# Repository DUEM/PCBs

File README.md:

# PCBs
A working record of DUSC PCBs and the DUEM KiCad library. Hopefully this way we can keep KiCad happy by all singing from the same ~~hymnsheet~~ netlist. Old and not necessarily a complete set of PCBs live in `oldPCBs`.

Remember to store final designs on the DUSC drive.

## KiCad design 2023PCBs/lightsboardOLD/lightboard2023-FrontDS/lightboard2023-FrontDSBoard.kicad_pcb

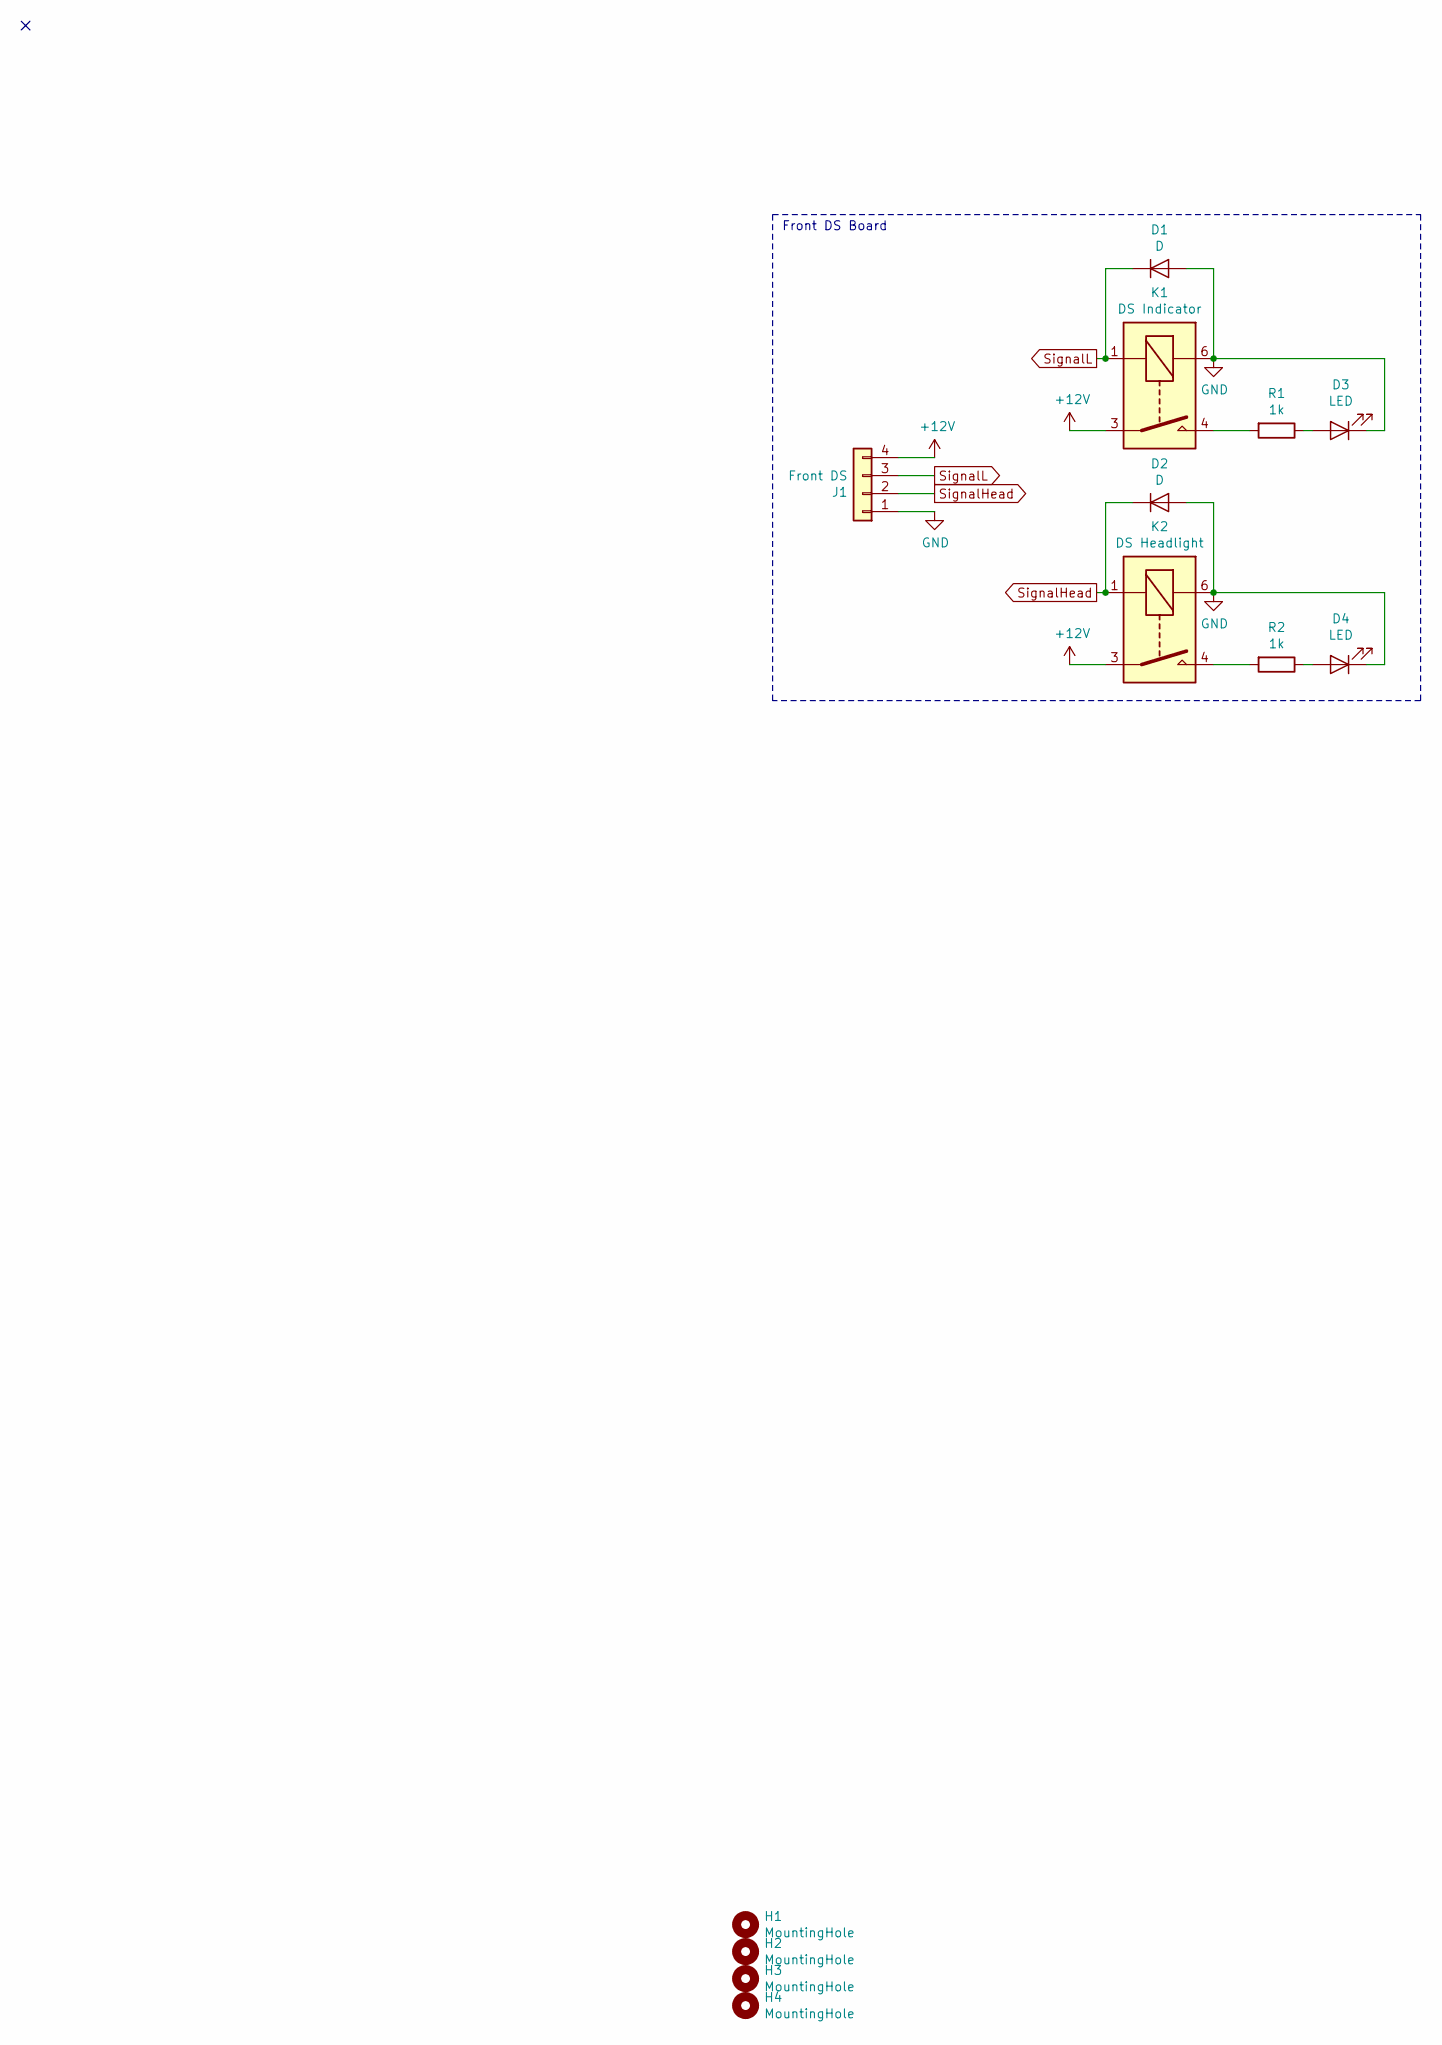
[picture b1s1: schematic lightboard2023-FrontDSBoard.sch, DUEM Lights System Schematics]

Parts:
D1, D2: D; D_DO-41_SOD81_P10.16mm_Horizontal
D3, D4: LED; flywire_2
H1, H2, H3, H4: MountingHole; MountingHole_2.7mm
J1: Front DS; Phoenix_4Way_P2.5mm
K1: DS Indicator; DK_Relay
K2: DS Headlight; DK_Relay
R1, R2: 1k; R_Axial_DIN0207_L6.3mm_D2.5mm_P10.16mm_Horizontal

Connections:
+12V: J1.4, K1.3, K2.3
GND: D1.2 (A), D2.2 (A), D3.1 (K), D4.1 (K), J1.1, K1.6, K2.6
unnamed: D3.2 (A), R1.1
unnamed: D4.2 (A), R2.1
unnamed: K1.4, R1.2
unnamed: K2.4, R2.2
SignalHead: D2.1 (K), J1.2, K2.1
SignalL: D1.1 (K), J1.3, K1.1

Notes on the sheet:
Front DS Board

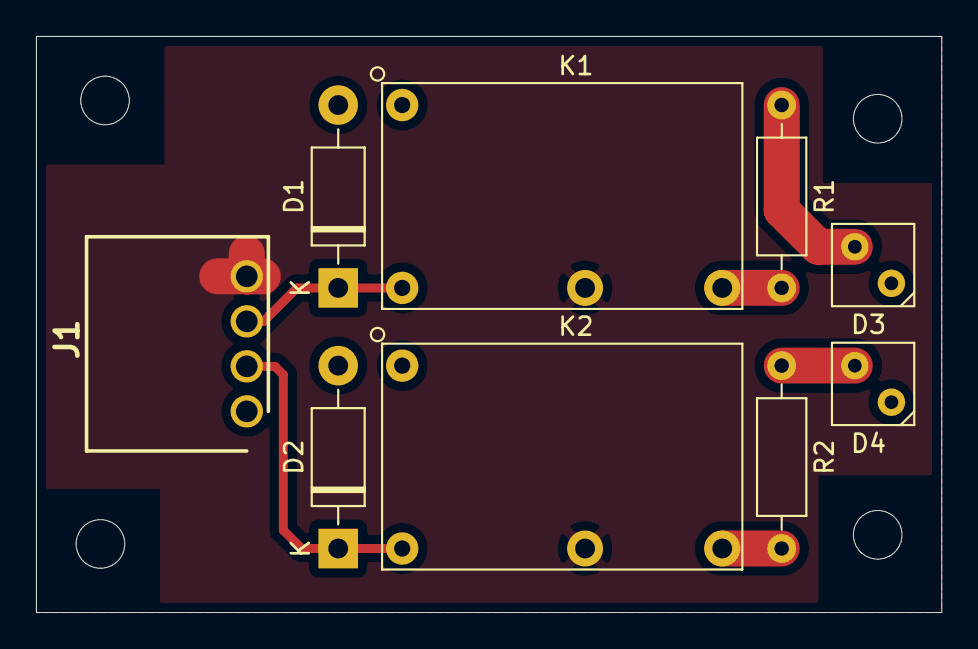
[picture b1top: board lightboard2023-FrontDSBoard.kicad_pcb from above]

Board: 2 copper layers, 50.3 x 32.0 mm, 13 parts (0 on the bottom side), 8 nets.

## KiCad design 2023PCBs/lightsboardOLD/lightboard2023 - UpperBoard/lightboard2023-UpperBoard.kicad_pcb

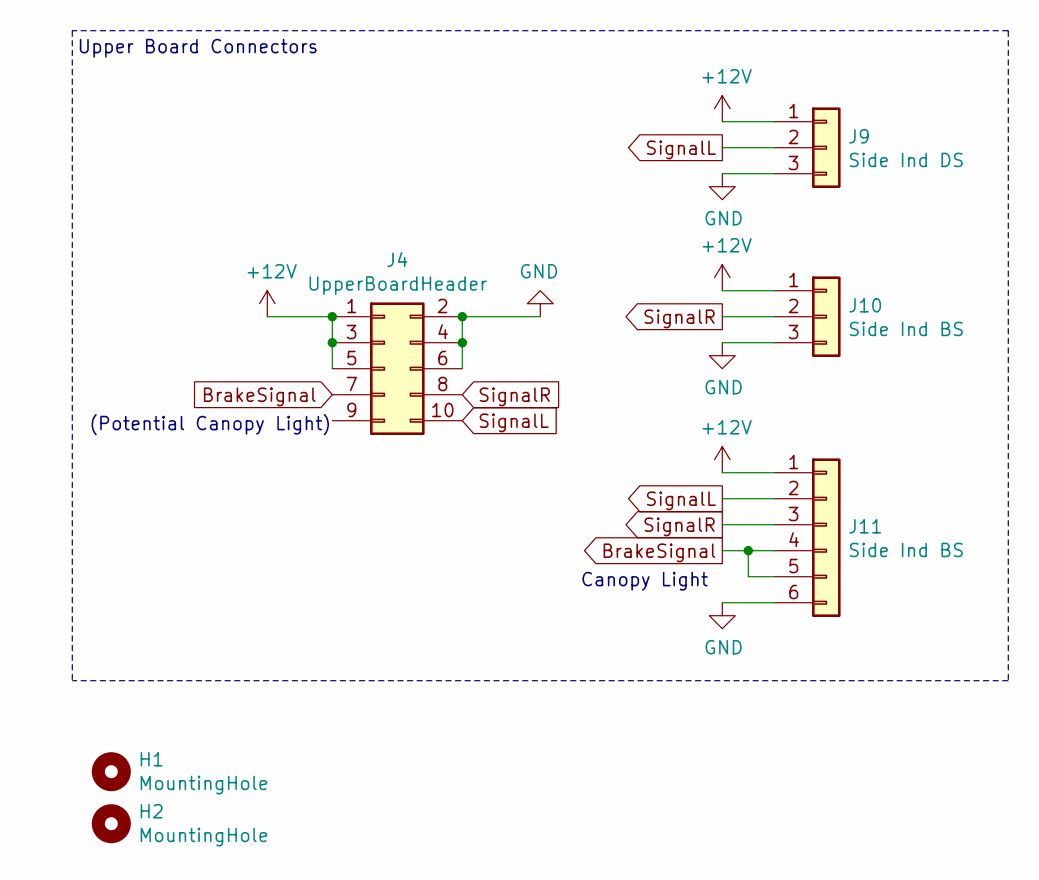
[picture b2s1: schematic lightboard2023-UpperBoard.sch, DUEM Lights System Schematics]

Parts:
H1, H2: MountingHole; MountingHole_2.7mm
J4: UpperBoardHeader; PinHeader_2x05_P2.54mm_Vertical
J9: Side Ind DS; Phoenix_3Way_P2.5mm
J10: Side Ind BS; Phoenix_3Way_P2.5mm
J11: Side Ind BS; Phoenix_6Way_P2.5mm

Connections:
+12V: J4.1, J4.3, J4.5, J9.1, J10.1, J11.1
BrakeSignal: J4.7, J11.4, J11.5
GND: J4.2, J4.4, J4.6, J9.3, J10.3, J11.6
SignalL: J4.10, J9.2, J11.2
SignalR: J4.8, J10.2, J11.3

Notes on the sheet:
Upper Board Connectors
(Potential Canopy Light)
Canopy Light

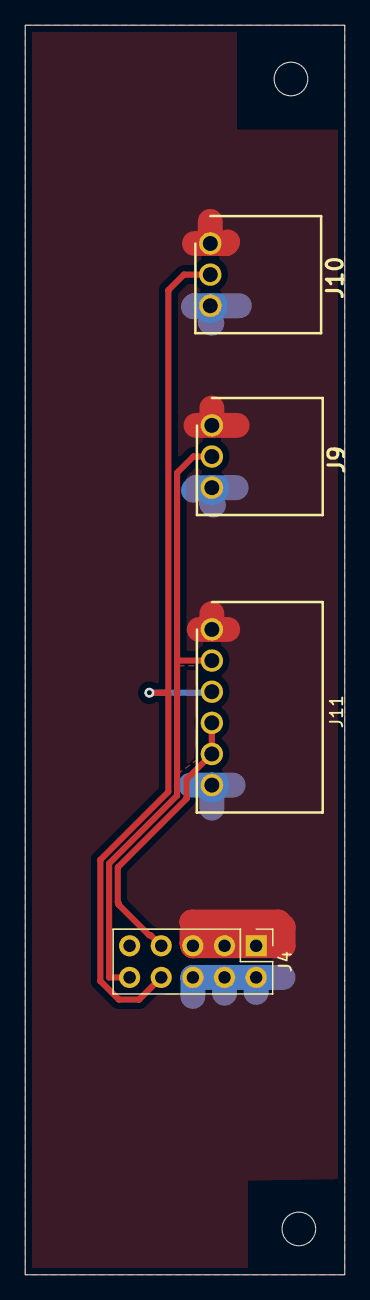
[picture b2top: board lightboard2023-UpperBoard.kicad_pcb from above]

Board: 2 copper layers, 25.7 x 100.3 mm, 6 parts (0 on the bottom side), 5 nets.

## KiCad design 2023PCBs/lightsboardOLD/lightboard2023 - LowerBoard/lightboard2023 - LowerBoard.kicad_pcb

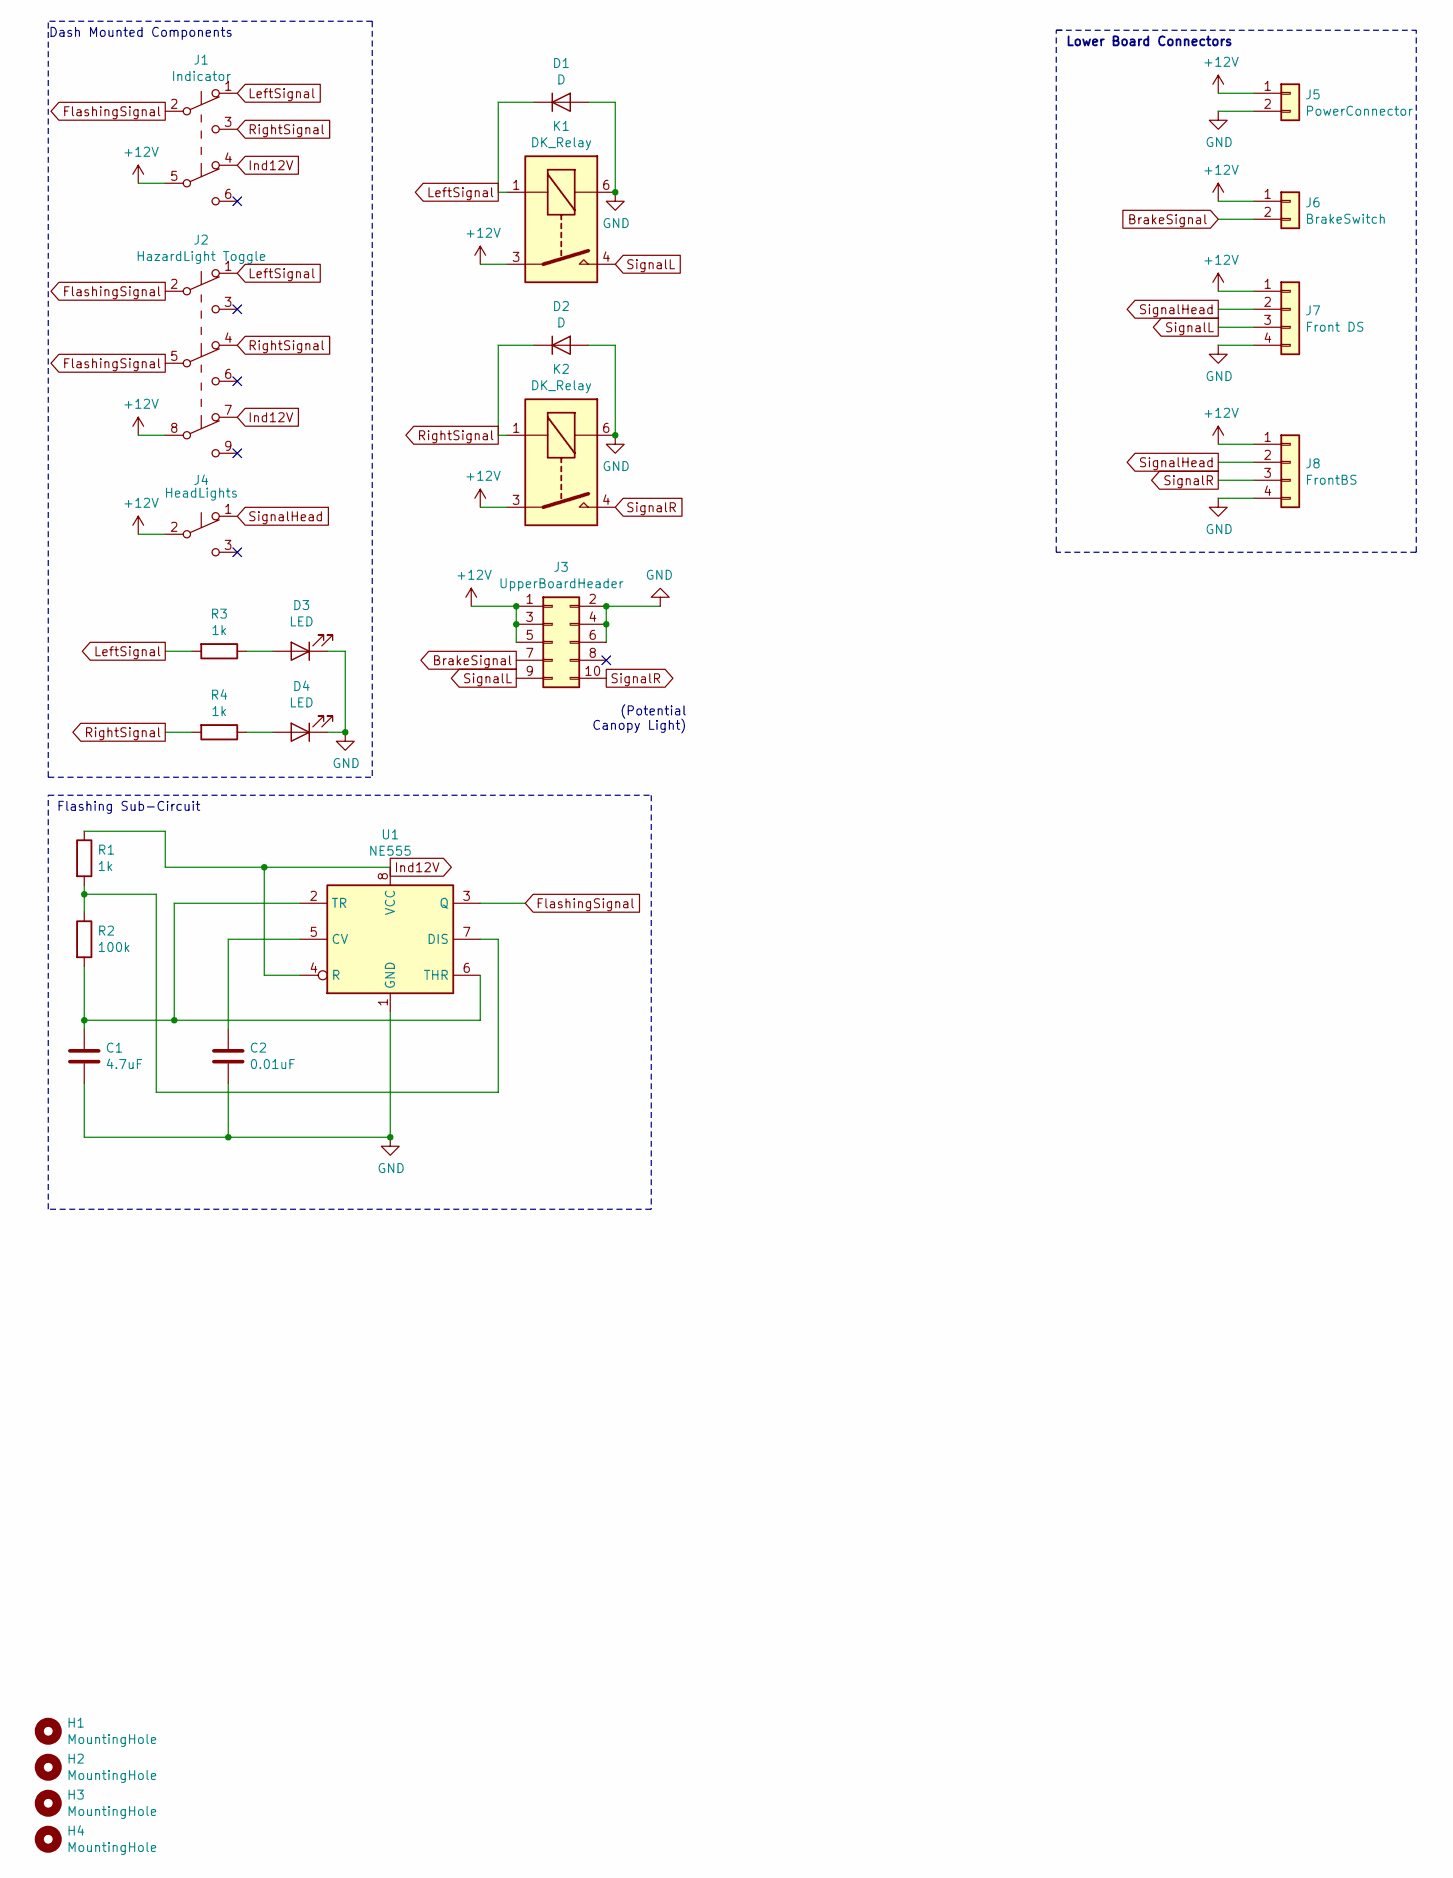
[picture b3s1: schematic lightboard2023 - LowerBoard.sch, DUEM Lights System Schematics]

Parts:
C1: 4.7uF; CP_Radial_D5.0mm_P2.50mm
C2: 0.01uF; CP_Radial_D5.0mm_P2.50mm
D1, D2: D; D_DO-41_SOD81_P10.16mm_Horizontal
D3, D4: LED; flywire_2
H1, H2, H3, H4: MountingHole; MountingHole_2.7mm
J1: Indicator; flywire_5
J2: HazardLight Toggle; flywire_6_special_haz
J3: UpperBoardHeader; PinHeader_2x05_P2.54mm_Vertical
J4: HeadLights; flywire_3
J5: PowerConnector; Phoenix_2Way_P2.5mm
J6: BrakeSwitch; Phoenix_2Way_P2.5mm
J7: Front DS; Phoenix_4Way_P2.5mm
J8: FrontBS; Phoenix_4Way_P2.5mm
K1, K2: DK_Relay
R1, R3, R4: 1k; R_Axial_DIN0207_L6.3mm_D2.5mm_P10.16mm_Horizontal
R2: 100k; R_Axial_DIN0207_L6.3mm_D2.5mm_P10.16mm_Horizontal
U1: NE555; DIP-8_W7.62mm_Socket

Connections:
+12V: J1.5 (B), J2.8 (B), J3.1, J3.3, J3.5, J4.2 (B), J5.1, J6.1, J7.1, J8.1, K1.3, K2.3
BrakeSignal: J3.7, J6.2
FlashingSignal: J1.2 (B), J2.2 (B), J2.5 (B), U1.3 (Q)
GND: C1.2, C2.2, D1.2 (A), D2.2 (A), D3.1 (K), D4.1 (K), J3.2, J3.4, J3.6, J5.2, J7.4, J8.4, K1.6, K2.6, U1.1 (GND)
Ind12V: J1.4 (A), J2.7 (A), R1.1, U1.4 (R), U1.8 (VCC)
LeftSignal: D1.1 (K), J1.1 (A), J2.1 (A), K1.1, R3.2
unnamed: C1.1, R2.2, U1.2 (TR), U1.6 (THR)
unnamed: C2.1, U1.5 (CV)
unnamed: D3.2 (A), R3.1
unnamed: D4.2 (A), R4.1
unnamed: R1.2, R2.1, U1.7 (DIS)
RightSignal: D2.1 (K), J1.3 (C), J2.4 (A), K2.1, R4.2
SignalHead: J4.1 (A), J7.2, J8.2
SignalL: J3.9, J7.3, K1.4
SignalR: J3.10, J8.3, K2.4

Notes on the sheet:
Lower Board Connectors
(Potential Canopy Light)
Flashing Sub-Circuit
Dash Mounted Components

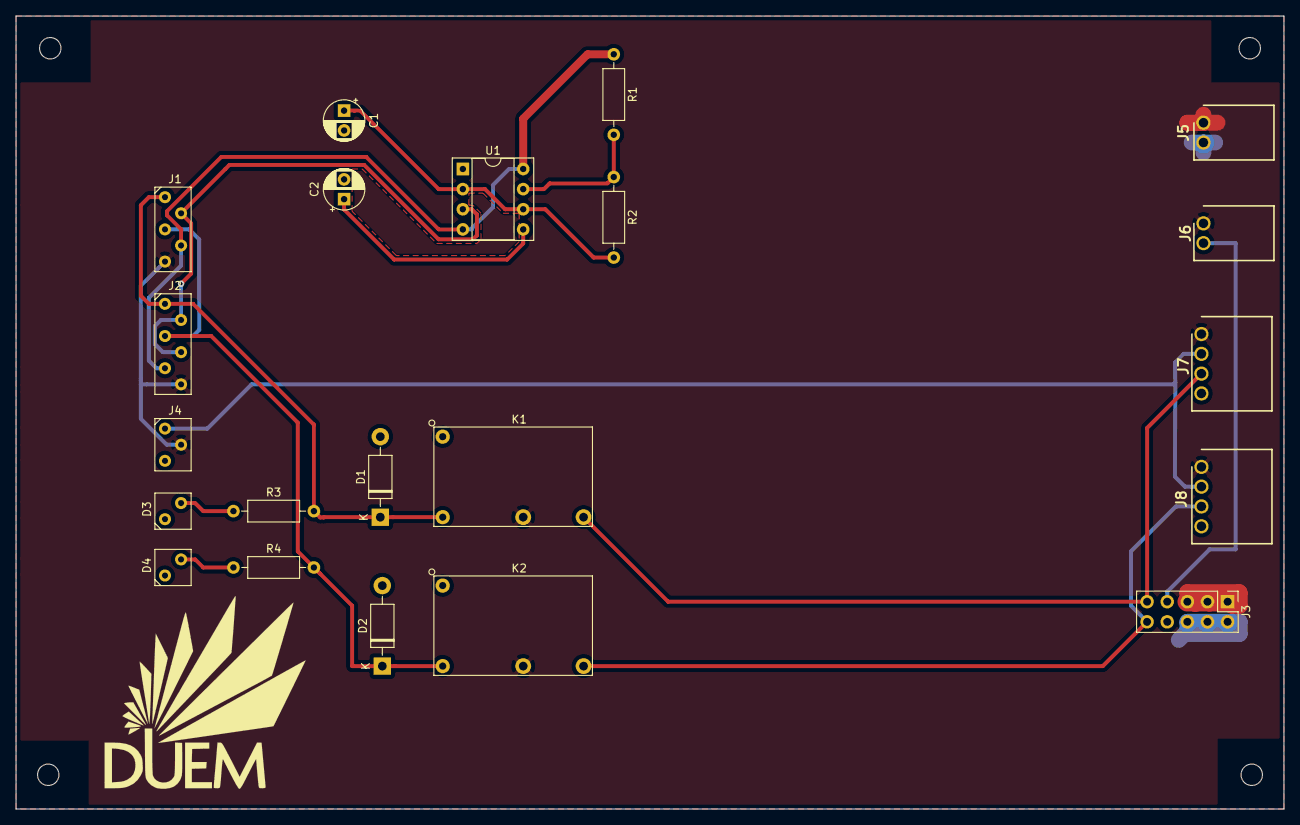
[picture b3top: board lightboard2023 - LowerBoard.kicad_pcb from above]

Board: 2 copper layers, 160.0 x 100.1 mm, 25 parts (0 on the bottom side), 15 nets.

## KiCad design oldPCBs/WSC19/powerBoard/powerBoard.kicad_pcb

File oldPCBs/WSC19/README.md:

# WSC19
Am going to try and put the original WSC19 design files in here. KiCad will probably cry when you open these... hopefully demonstrating why we're trying to use a global KiCad library instead now.

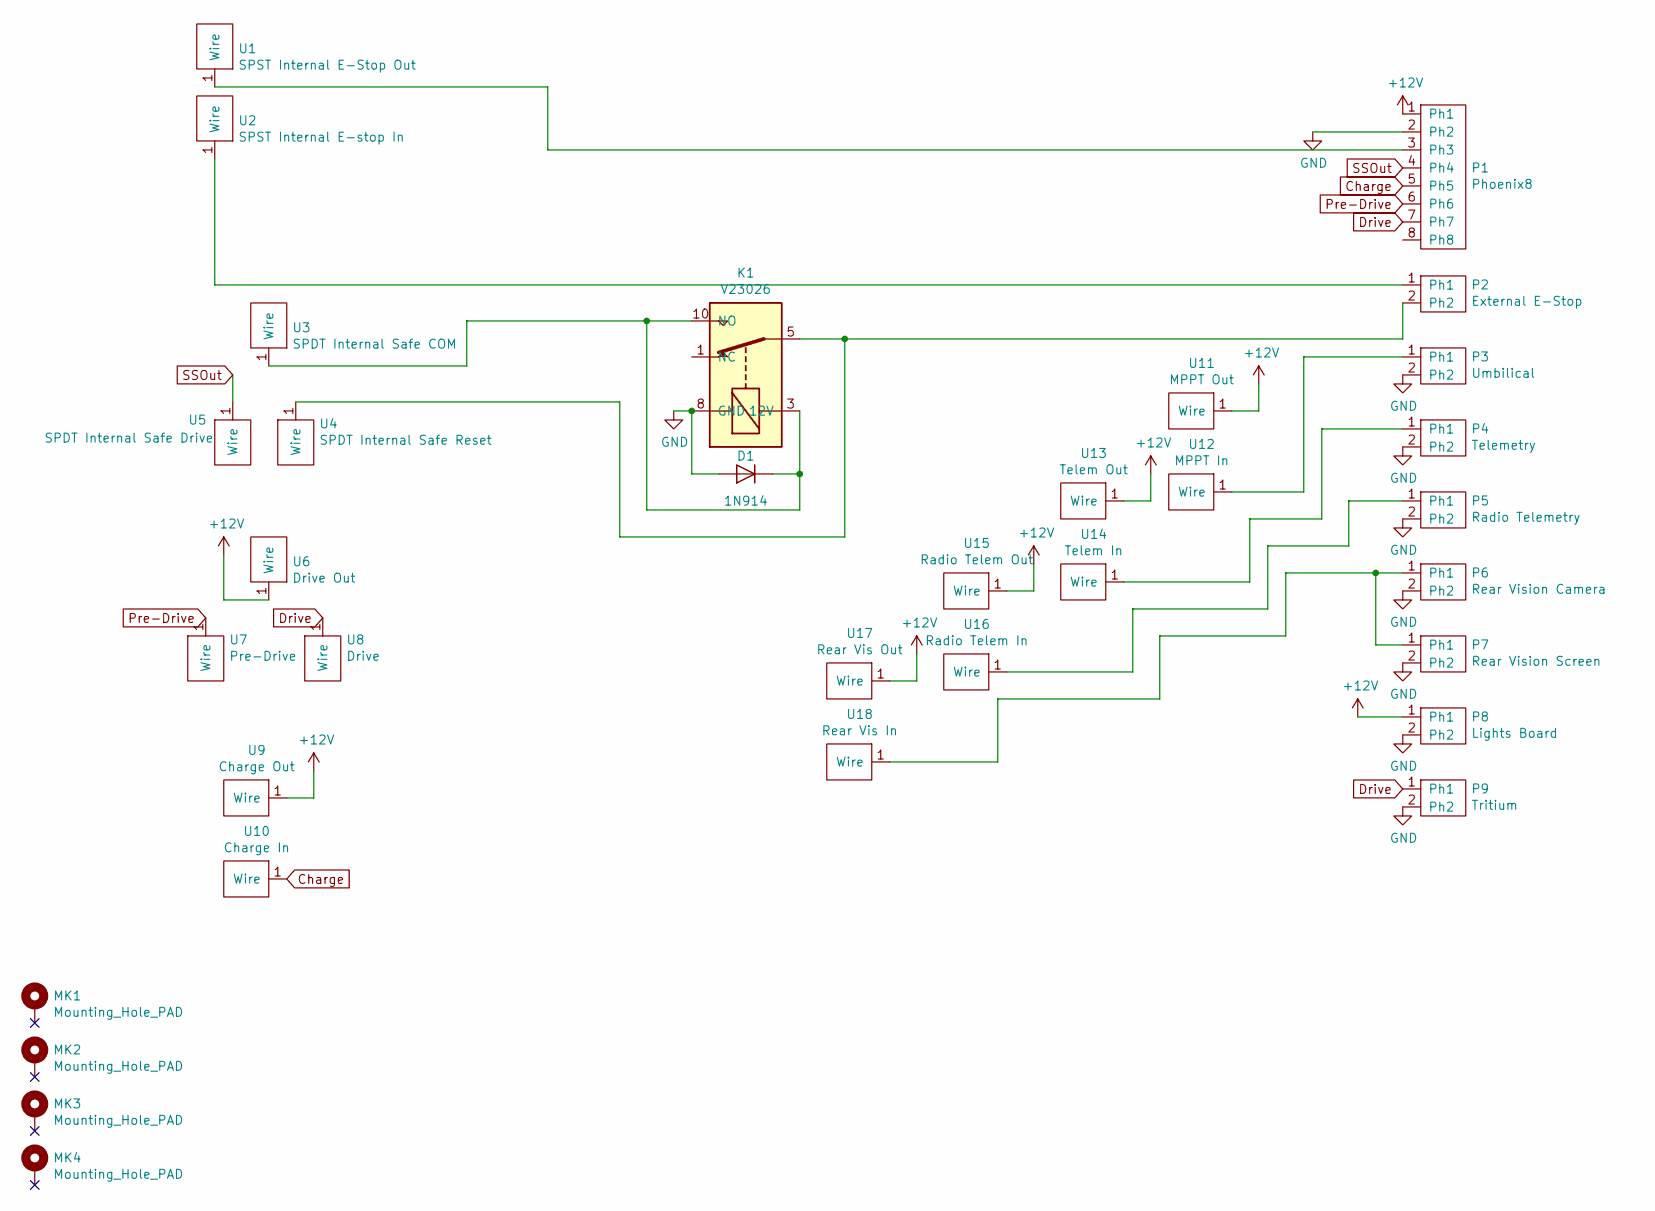
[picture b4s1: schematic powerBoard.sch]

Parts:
D1: 1N914; D_DO-35_SOD27_P7.62mm_Horizontal
K1: V23026; V23026 MONO
MK1, MK2, MK3, MK4: Mounting_Hole_PAD; MountingHole_2.7mm
P1: Phoenix8; PhoenixSmol8
P2: External E-Stop; PhoenixSmol2
P3: Umbilical; PhoenixSmol2
P4: Telemetry; PhoenixSmol2
P5: Radio Telemetry; PhoenixSmol2
P6: Rear Vision Camera; PhoenixSmol2
P7: Rear Vision Screen; PhoenixSmol2
P8: Lights Board; PhoenixSmol2
P9: Tritium; PhoenixSmol2
U1: SPST Internal E-Stop Out; SolderWirePad_1x01_Drill1.5mm
U2: SPST Internal E-stop In; SolderWirePad_1x01_Drill1.5mm
U3: SPDT Internal Safe COM; SolderWirePad_1x01_Drill1.5mm
U4: SPDT Internal Safe Reset; SolderWirePad_1x01_Drill1.5mm
U5: SPDT Internal Safe Drive; SolderWirePad_1x01_Drill1.5mm
U6: Drive Out; SolderWirePad_1x01_Drill1.5mm
U7: Pre-Drive; SolderWirePad_1x01_Drill1.5mm
U8: Drive; SolderWirePad_1x01_Drill1.5mm
U9: Charge Out; SolderWirePad_1x01_Drill1.5mm
U10: Charge In; SolderWirePad_1x01_Drill1.5mm
U11: MPPT Out; SolderWirePad_1x01_Drill1.5mm
U12: MPPT In; SolderWirePad_1x01_Drill1.5mm
U13: Telem Out; SolderWirePad_1x01_Drill1.5mm
U14: Telem In; SolderWirePad_1x01_Drill1.5mm
U15: Radio Telem Out; SolderWirePad_1x01_Drill1.5mm
U16: Radio Telem In; SolderWirePad_1x01_Drill1.5mm
U17: Rear Vis Out; SolderWirePad_1x01_Drill1.5mm
U18: Rear Vis In; SolderWirePad_1x01_Drill1.5mm

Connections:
+12V: P1.1 (Ph1), P8.1 (Ph1), U6.1, U9.1, U11.1, U13.1, U15.1, U17.1
Charge: P1.5 (Ph5), U10.1
Drive: P1.7 (Ph7), P9.1 (Ph1), U8.1
GND: D1.2 (A), K1.8 (GND), P1.2 (Ph2), P3.2 (Ph2), P4.2 (Ph2), P5.2 (Ph2), P6.2 (Ph2), P7.2 (Ph2), P8.2 (Ph2), P9.2 (Ph2)
unnamed: D1.1 (K), K1.3 (12V), K1.10 (NO), U3.1
unnamed: K1.5, P2.2 (Ph2), U4.1
unnamed: P1.3 (Ph3), U1.1
unnamed: P2.1 (Ph1), U2.1
unnamed: P3.1 (Ph1), U12.1
unnamed: P4.1 (Ph1), U14.1
unnamed: P5.1 (Ph1), U16.1
unnamed: P6.1 (Ph1), P7.1 (Ph1), U18.1
Pre-Drive: P1.6 (Ph6), U7.1
SSOut: P1.4 (Ph4), U5.1

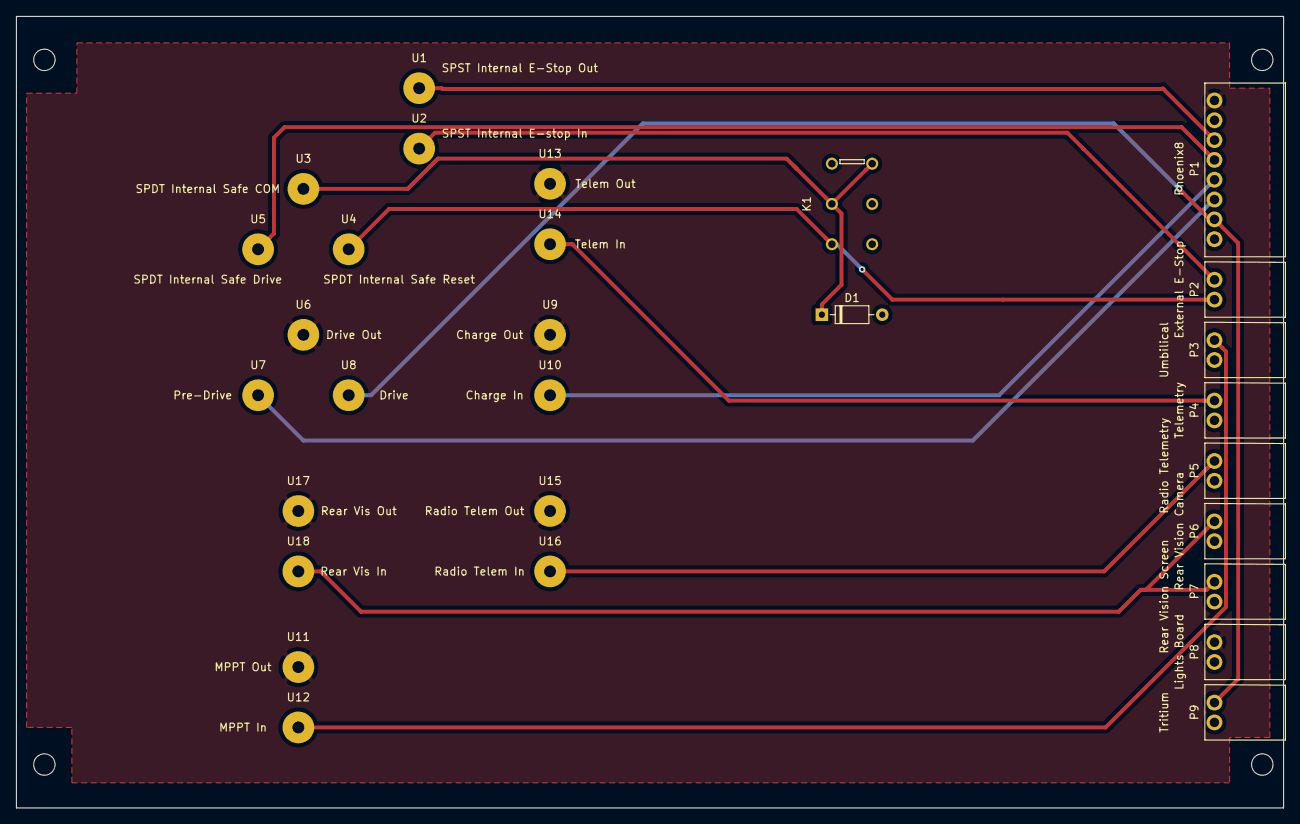
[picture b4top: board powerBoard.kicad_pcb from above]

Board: 2 copper layers, 159.9 x 99.9 mm, 33 parts (0 on the bottom side), 14 nets.

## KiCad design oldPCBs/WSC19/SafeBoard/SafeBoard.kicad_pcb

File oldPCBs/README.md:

# The PCB Graveyard
Where old PCBs go to die...

Probably a good idea to actually order these properly like...
1. WSC19
1. ESC20
1. ASC21

...and not have to many rogue versions floating around. Once this is done can get rid of `.zip` files.

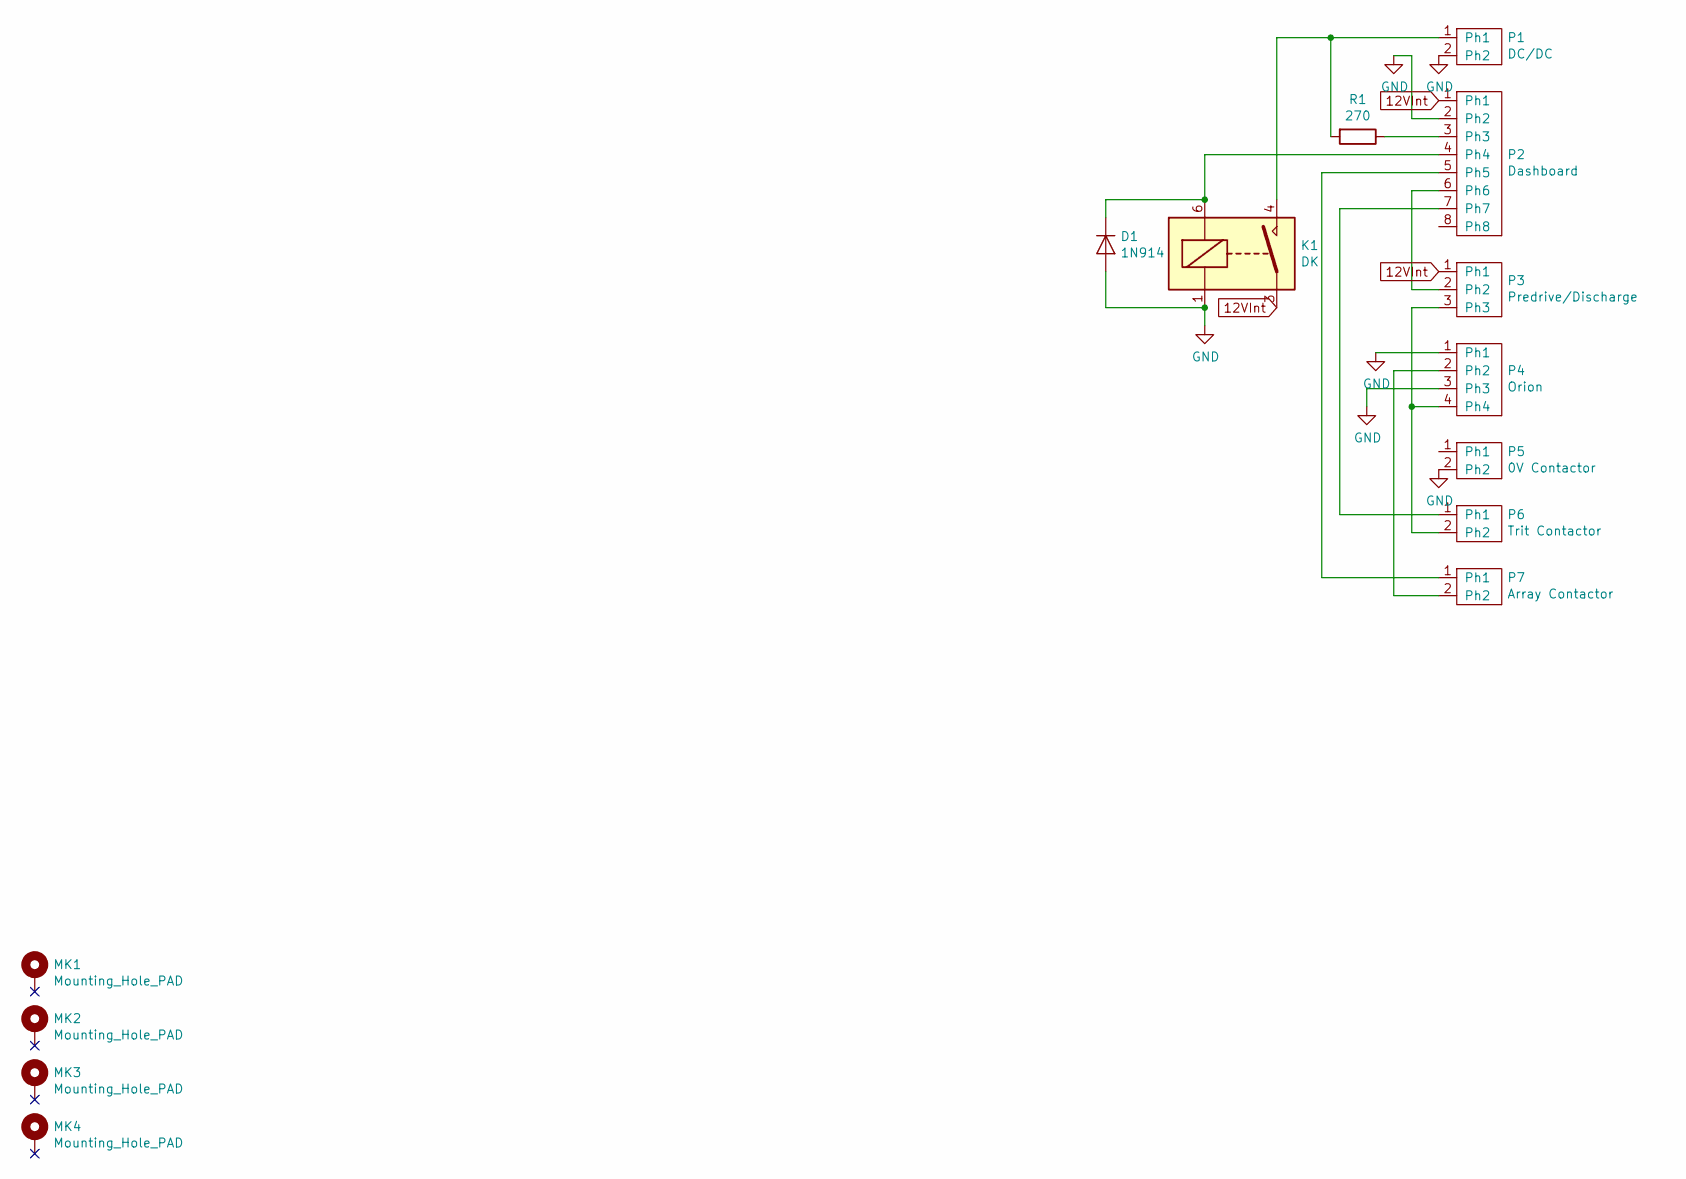
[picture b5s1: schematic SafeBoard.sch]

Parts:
D1: 1N914; D_DO-35_SOD27_P7.62mm_Horizontal
K1: DK; DKRelay
MK1, MK2, MK3, MK4: Mounting_Hole_PAD; MountingHole_2.7mm
P1: DC/DC; PhoenixSmol2
P2: Dashboard; PhoenixSmol8
P3: Predrive/Discharge; PhoenixSmol3
P4: Orion; PhoenixSmol4
P5: 0V Contactor; PhoenixSmol2
P6: Trit Contactor; PhoenixSmol2
P7: Array Contactor; PhoenixSmol2
R1: 270; R_Axial_DIN0207_L6.3mm_D2.5mm_P15.24mm_Horizontal

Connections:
12VInt: K1.3, P2.1 (Ph1), P3.1 (Ph1)
GND: D1.2 (A), K1.1, P1.2 (Ph2), P2.2 (Ph2), P4.1 (Ph1), P4.3 (Ph3), P5.2 (Ph2)
unnamed: D1.1 (K), K1.6, P2.4 (Ph4)
unnamed: K1.4, P1.1 (Ph1), R1.2
unnamed: P2.3 (Ph3), R1.1
unnamed: P2.5 (Ph5), P7.1 (Ph1)
unnamed: P2.6 (Ph6), P3.2 (Ph2)
unnamed: P2.7 (Ph7), P6.1 (Ph1)
unnamed: P3.3 (Ph3), P4.4 (Ph4), P6.2 (Ph2)
unnamed: P4.2 (Ph2), P7.2 (Ph2)

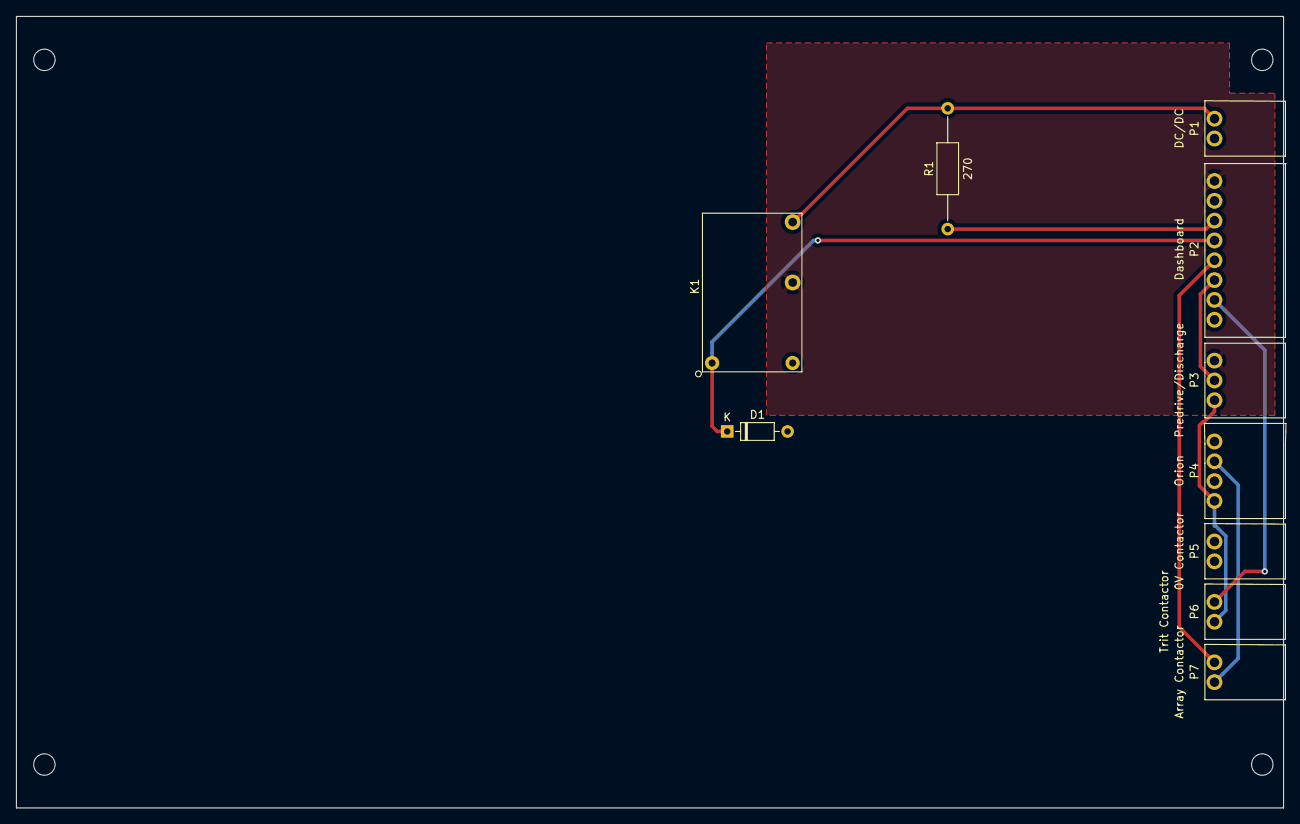
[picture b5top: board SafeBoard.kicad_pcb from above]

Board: 2 copper layers, 159.9 x 99.9 mm, 14 parts (0 on the bottom side), 10 nets.

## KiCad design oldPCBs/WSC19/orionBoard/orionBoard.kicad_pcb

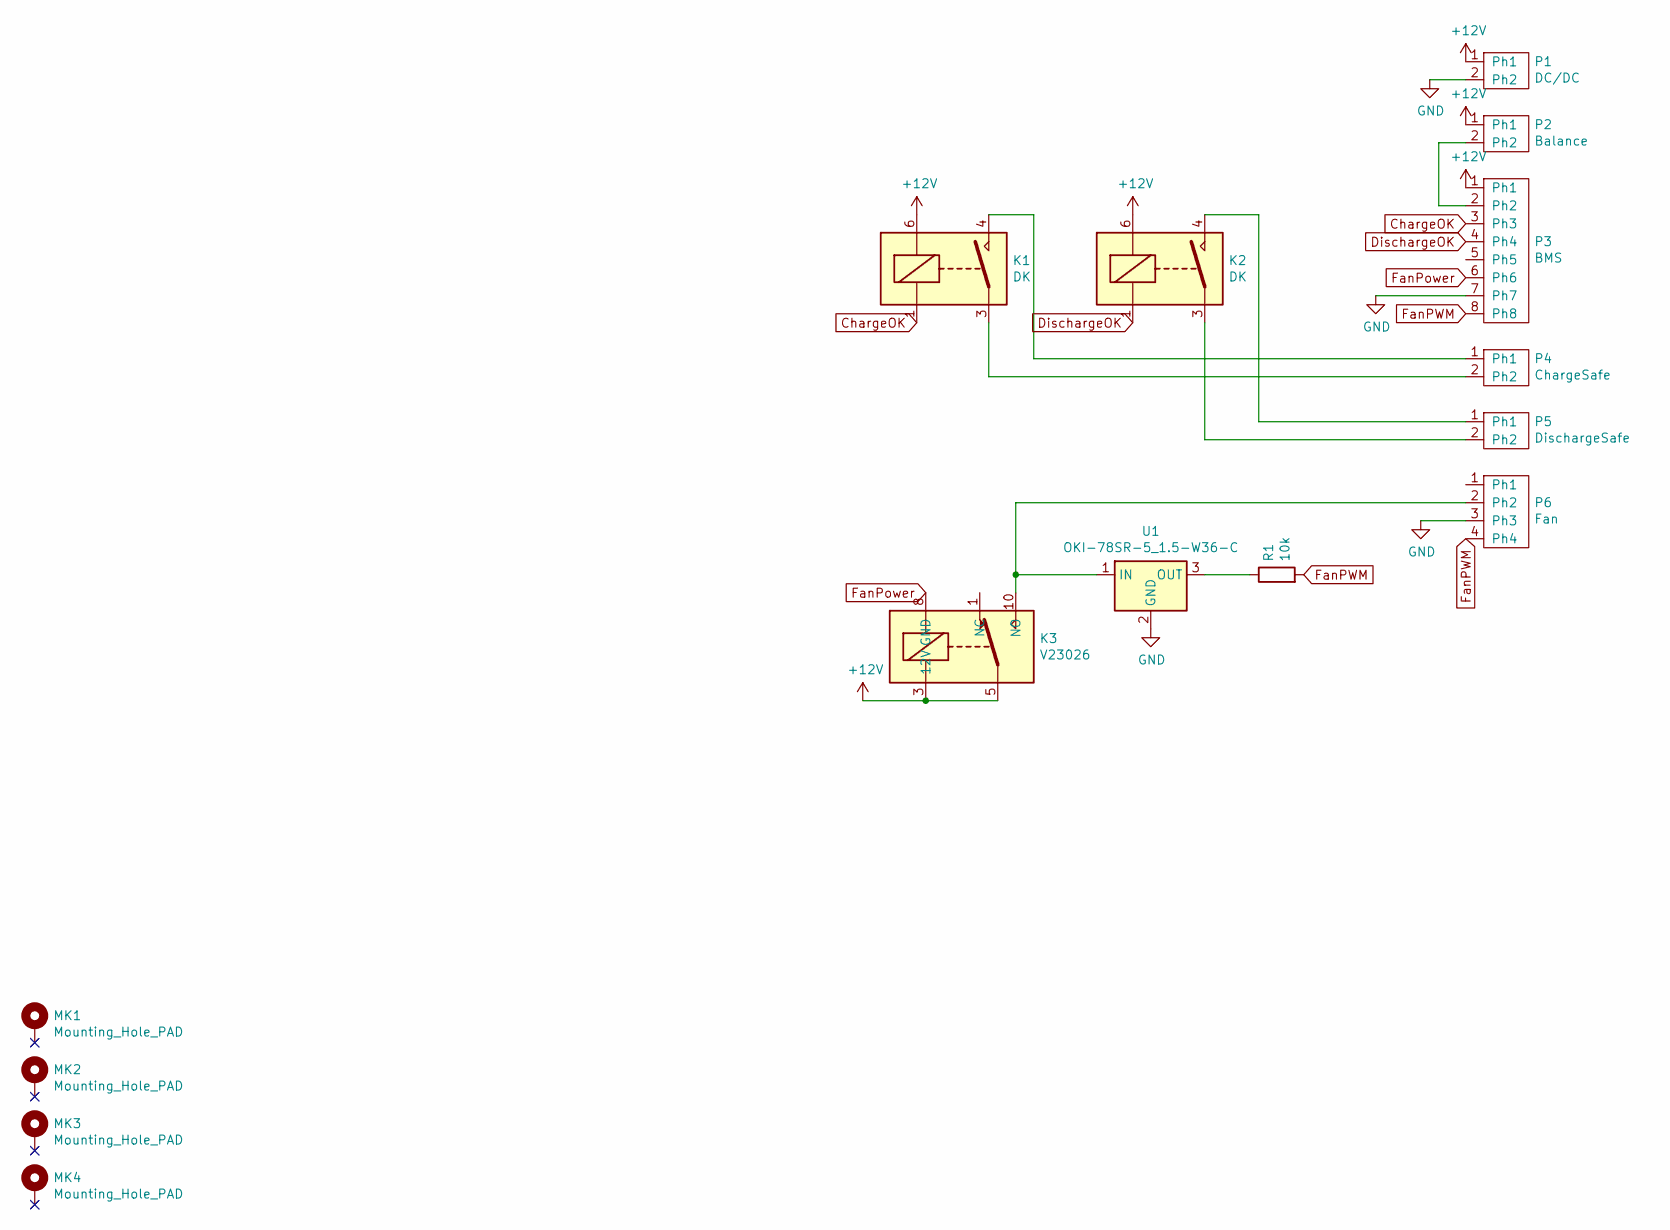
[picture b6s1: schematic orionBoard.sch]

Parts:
K1, K2: DK; DKRelay
K3: V23026; V23026 MONO
MK1, MK2, MK3, MK4: Mounting_Hole_PAD; MountingHole_2.7mm
P1: DC/DC; PhoenixSmol2
P2: Balance; PhoenixSmol2
P3: BMS; PhoenixSmol8
P4: ChargeSafe; PhoenixSmol2
P5: DischargeSafe; PhoenixSmol2
P6: Fan; PhoenixSmol4
R1: 10k; R_Axial_DIN0207_L6.3mm_D2.5mm_P15.24mm_Horizontal
U1: OKI-78SR-5_1.5-W36-C; Converter_DCDC_muRata_OKI-78SR_Vertical

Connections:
+12V: K1.6, K2.6, K3.3 (12V), K3.5, P1.1 (Ph1), P2.1 (Ph1), P3.1 (Ph1)
ChargeOK: K1.1, P3.3 (Ph3)
DischargeOK: K2.1, P3.4 (Ph4)
FanPWM: P3.8 (Ph8), P6.4 (Ph4), R1.2
FanPower: K3.8 (GND), P3.6 (Ph6)
GND: P1.2 (Ph2), P3.7 (Ph7), P6.3 (Ph3), U1.2 (GND)
unnamed: K1.3, P4.2 (Ph2)
unnamed: K1.4, P4.1 (Ph1)
unnamed: K2.3, P5.2 (Ph2)
unnamed: K2.4, P5.1 (Ph1)
unnamed: K3.10 (NO), P6.2 (Ph2), U1.1 (IN)
unnamed: P2.2 (Ph2), P3.2 (Ph2)
unnamed: R1.1, U1.3 (OUT)

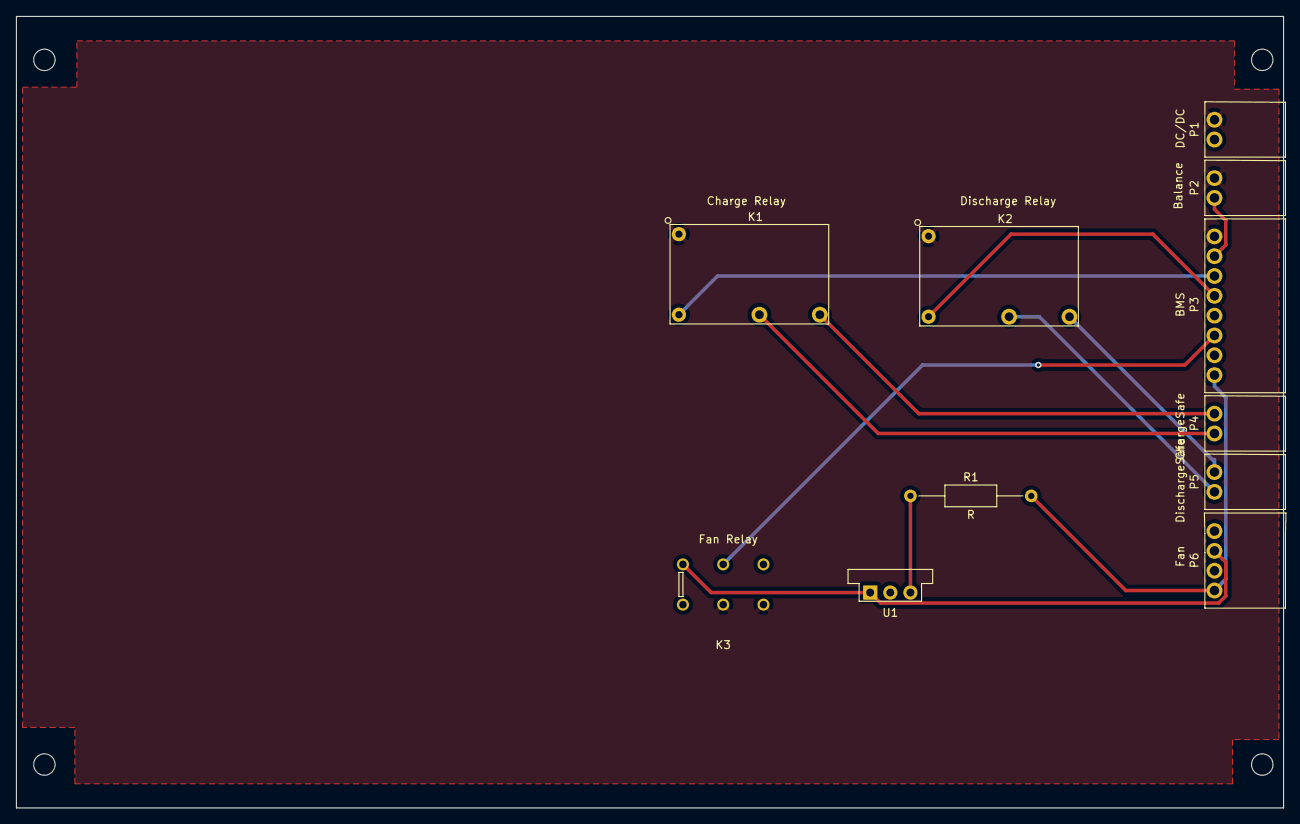
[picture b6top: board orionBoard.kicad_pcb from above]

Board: 2 copper layers, 159.9 x 99.9 mm, 15 parts (0 on the bottom side), 13 nets.

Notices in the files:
parts and their libraries:
Copyright 2016 Accelerated Designs. All rights reserved.
